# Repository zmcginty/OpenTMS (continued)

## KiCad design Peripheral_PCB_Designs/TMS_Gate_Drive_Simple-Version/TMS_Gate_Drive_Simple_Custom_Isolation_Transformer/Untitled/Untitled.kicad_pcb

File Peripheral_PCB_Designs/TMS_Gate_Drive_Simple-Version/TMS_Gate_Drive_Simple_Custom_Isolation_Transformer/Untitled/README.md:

# FZ1200R33KF2 bolt-on gate driver (rev D, prototype)

Single-channel plug-and-play style gate driver for the Infineon/eupec FZ1200R33KF2
(3300 V / 1200 A IHM single switch). Same external interface as the CONCEPT 1SD418F2:
15 V supply on a 5-pin header (or JST-XH), fiber-optic command in, fiber-optic status out,
2-level / 3-level mode jumper. Built only from catalog parts, with no custom-wound magnetics and no
CONCEPT / Power Integrations ASICs, cores or DC/DC modules. Dynamic advanced active clamping follows the idea used in the
1SP0635 (SCALE-2 plug-and-play).

**Status: design draft, not built or tested. Hazardous voltages. Read "Open items" before ordering anything.**

## Files

| File | What it is |
|---|---|
| `fz1200_gate_driver.kicad_pro/.kicad_sch/.kicad_pcb` | KiCad 7 project (opens in KiCad 8/9; they upgrade it) |
| `power.kicad_sch`, `control.kicad_sch`, `output.kicad_sch` | Sub-sheets: isolation supply, protection logic, output stage + HV |
| `igbt_drv.kicad_sym`, `igbt_drv.pretty/` | Project symbol library and custom footprints (incl. the provisional XS000027 land pattern) |
| `BOM_fz1200_gate_driver.csv` | Grouped BOM (Qty 0 = DNP) |
| `out/` | Gerbers + drill (6 layers), pick-and-place CSV, schematic PDF, per-layer PCB PDFs |
| `generator/` | Python that generates schematic, PCB, routing and BOM from `circuit.py`; `mech.py` holds the mount coordinates |

The schematic and board are generated, so changes are easiest made in `generator/circuit.py`
(parts and nets) and `generator/gen_pcb.py` (placement), then re-run
`python3 generator/gen_sch.py`, `/usr/bin/python3 generator/gen_pcb.py`,
`/usr/bin/python3 generator/patch_fix.py fz1200_gate_driver.kicad_pcb` (CH6 neck-downs and primary ground stitching),
`/usr/bin/python3 generator/fill_zones.py ...`, `/usr/bin/python3 generator/drc.py fz1200_gate_driver.kicad_pcb drc.rpt`,
`/usr/bin/python3 generator/finish.py fz1200_gate_driver.kicad_pcb drc.rpt` (closes the few connections the router leaves open),
`/usr/bin/python3 generator/manual_fix.py fz1200_gate_driver.kicad_pcb drc.rpt` (via-bridges anything still open),
`/usr/bin/python3 generator/cleanup.py fz1200_gate_driver.kicad_pcb`, `/usr/bin/python3 generator/fill_zones.py fz1200_gate_driver.kicad_pcb`,
`python3 generator/gen_bom.py`, `sh generator/export.sh`. If an edit leaves a few opens that finish/manual_fix can't close, `generator/maze_fix.py board drc.rpt` is a fine-grid maze router for them. `python3 generator/check_sides.py` confirms no net crosses the isolation barrier.
You can also just edit the KiCad files by hand from here on.

## Interface (matches 1SD418F2)

| Item | This design | 1SD418F2 |
|---|---|---|
| Supply | J1 1x5 2.54 mm: pin 3 = +15 V, pins 1, 2, 4, 5 = GND (or J2 JST-XH: 1 = +15 V, 2 = GND) | same 5-pin pinout |
| Command | HFBR-2522Z, light = IGBT on | HFBR-2522 |
| Status | HFBR-1522Z, light on = healthy, 0.9 us dark ack on every command edge, about 1.1 s dark on fault | same protocol (1 s) |
| Mode | JP1 1-2 = 2-level (driver turns off on short circuit), 2-3 = 3-level (report only, host turns off). Open = 2-level | J1 jumper, same meaning |
| Gate | +15 / -10 V (set by the catalog transformer), Rg(on) 1.8 ohm, Rg(off) 3.4 ohm, Cge 222 nF | +-15 V, 1.8 / 3.4 ohm, 220 nF |
| Mounting | Screws onto the module G, aux E, aux C terminals (M4), plus a 3.2 mm support hole; terminal positions and outline as on the 1SP0635 (see Board) | same principle |

## Architecture

- **Isolation supply:** TI SN6507 push-pull driver (36 V, two 0.5 A switches, 150 kHz set by R1,
  soft-start and current limit on SS/ILIM) driving a **Poweronics XS000027**, a catalog gate-drive
  transformer for IGBTs up to 3.3 kV: 6 kV isolation test, partial-discharge routine test at 3.545 kV,
  18 kV impulse, 15-0-10 V output, 10 W from a 15 V supply. Rails: VP = +15 V, VE = emitter,
  VEE = -10 V, unregulated (the 1SD418F2 is unregulated too). D3 rectifies the 15 V end and D6 the 10 V end;
  D4/D5 are DNP positions in case Poweronics' reference rectifier uses all four diodes.
- **Logic** is referenced to VEE (the -10 V rail) with a 5 V LDO, so the fiber parts, comparators,
  gates and both gate-driver ICs share one ground with no level shifting.
- **Gate power stage (rev D): Q2 = Infineon ISA170230C04LMDS**, a complementary 40 V OptiMOS dual in
  one SO-8 (N 17 mohm / 38 A pulsed, P 23 mohm / -35 A pulsed, VGS +-20 V), the same family as the
  ISA250250N04LMDS dual-N. Q2 is the only part that carries gate current:
  - **Turn-on:** Q2 P-channel, source at VP (+15 V), drain -> R40 || R41 (2 x 3.6 ohm) -> GATE.
    Its gate is driven between VP and VE (0 / -15 V VGS) by U21 (UCC27511, supplied VP-VE).
    The logic is VEE-referenced, so DRV_ON reaches U21 through a small level shifter:
    Q7 (IRLML0060) pulls LSIN down through R60, D20 (BAT54) clamps it at VE, R61 pulls it up to VP.
    If anything loses power, R61/R64 hold the P-FET off.
  - **Turn-off:** Q2 N-channel, source at VEE (-10 V), drain -> R47 || R48 (2 x 6.8 ohm) -> GATE,
    driven between VE and VEE (10 V VGS) by U22 (UCC27511).
  - Peak currents with these resistors: about 11 A on, 7 A off (25 V swing), so the 35/38 A pulse
    rating is margin. Lower Rg to get more current, the stage is not the limit.
  - C50 (10 uF) and C51 sit right at Q2's two source pins, so the high-current loop is VP-C50-VEE.
  - Why not two ISA250250N04LMDS N-channels: an N-FET high side needs its gate above VP, i.e. a
    bootstrap or charge pump, and a bootstrap can't hold the IGBT on indefinitely (DC on, or long
    on-times at low frequency). The complementary sibling avoids that with the same package and pinout.
  **Soft shutdown** after a fault: Q3 (IRLML0060) through 10 ohm (normal off path held off).
- **Short-circuit (Vce) detection:** 6 x 3.3 Mohm high-voltage chain plus 309 kohm divider into a
  TLV3202 comparator. Trip at Vce = 55.1 V (1SD418F2: 50-60 V), blanking 6.1 us from the on command.
  The fault latches a 1.1 s TLC555 lockout and darkens the status fiber.
- **UVLO:** both rails watched (each comparator channel has its own LM4040 reference, D13/D14):
  VP-VEE trips at 21.5 V rising / 20.3 V falling (nominal 25 V), VE-VEE at 8.5 / 8.1 V (nominal 10 V).
  That's about 86 % of nominal, the same ratio as the 1SD418F2's 13 V threshold on its 15 V supply.
- **Advanced active clamping:** 6 x 1.5SMC440A TVS from collector to gate through SS34 + 10 ohm.
  When clamp current flows, Q4 pulls the gates of the turn-off switches (Q2, Q3) low, so the TVS
  current goes into the gate instead of the off-resistor. This is the "advanced" part.
- **Dynamic AAC (DA2C, as on 1SP0635):** an extra SMBJ188A is in series. Q5 (600 V) shorts it while
  the IGBT is on and for about 17 us after turn-off, then releases it. So the clamp acts at
  2508-2772 V during switching, but the module can sit at a higher DC link when it's off. Q5's gate is
  bootstrapped (C57) so it stays on while the clamp node rises during clamping.

## Key numbers (calculated; the clamp was also checked in a behavioural ngspice model)

| Item | Value |
|---|---|
| Clamp onset, switching (6 x VBR) | 2508-2772 V at 25 C |
| Clamp onset, off-state (DA2C released) | 2717-3003 V |
| TVS stand-off: switching / off-state | 2256 V / 2444 V (in the off state D40 sees at most its 231 V VBR max), so max DC link 2200 V (same as 1SD418F2) |
| Simulated Vce peak, 4 kA turn-off, 100 nH, BV +6 % hot | 2.96 kV (< 3.3 kV) |
| Desat threshold / blanking | 55.1 V / 6.08 us; gate starts falling about 6.3 us, well inside the 10 us SC rating |
| Gate energy per cycle (QG about 19 uC at -10/+15 V, estimated from the 22 uC at +-15 V, + Cge, 25 V swing) | about 0.61 mJ |
| Quiescent load | about 0.5 W (the status LED's 30 mA dominates) |
| Available output | about 6 W, set by the SN6507's 0.5 A switches at 15 V in (the XS000027 is rated 10 W) |
| Max switching frequency | **about 8 kHz** (1SD418F2: 4 kHz) |
| Status ack / fault block | 0.90 us / 1.1 s |

## Board

- 197.1 x 43.94 mm, outline and terminal positions taken from the 1SP0635V mechanical
  drawing (Description & Application Manual, Fig. 5), which bolts onto the same 3.3 kV IHM housing:
  - C (aux collector, X3): 20.04 mm from the left edge, 12.16 mm below the top edge
  - E (aux emitter, X2): C + 38.15 mm, 6.96 mm below the top edge
  - G (gate, X1): E + 21.00 mm, same height
  - 3.2 mm support hole: G + 114.4 mm, 3.95 mm above the bottom edge
  - The notches in the bottom edge and the cut-away under the right end follow the 1SP0635 outline.
    Corners without a dimension were scaled from the drawing (about 0.3 mm) and kept on or inside it.
  The layout follows the 1SP0635's arrangement too: HV chains at the collector (left) end, output
  stage around E/G, logic and fibers in the middle (fiber ports overhang the bottom edge), transformer and
  15 V input at the right end. Rev D: the fibers sit at 10.16 mm pitch so they interlock, and the
  comparator cluster (U19) moved to the bottom side above them, freeing the area under the gate power stage.
- 6 layers: F.Cu parts + signals | In1 VEE plane (PGND under the primary) | In2 signals |
  In3 signals + 5 V logic plane under the logic block | In4 VE (emitter) plane | B.Cu signals + parts.
  At this outline (about 30 % less usable area than rev A) four layers did not route. The comparator
  and UVLO clusters sit on the bottom side; the comparators are TLV3202 in SOIC-8 for easier escape.
- Primary-to-secondary: >= 20 mm copper-to-copper (measured 21.6 mm) with a 2 mm milled slot under T1 (1SD418F2: 20 mm).
- HV creepage is graded along both chains. Low-voltage copper keeps the IEC 60664-1 PD2 /
  material group II creepage for 3300 V (22 mm) from the collector chain. Between HV nets the
  spacing follows each pair's worst-case DC voltage at a 2200 V link, in both DA2C states
  (`generator/potentials.py`). Pairs under 400 V (only inside the Q5/D40 DA2C cluster, where the
  SOT-223 pin pitch alone is below the uncoated value) are held to the coated (IEC 60664-3) value.
  **So conformal coating is mandatory**, and so is FR4 with CTI >= 400.
  `generator/check_creepage.py` reports both the coated and uncoated results.
- Minimum copper clearance rule 0.15 mm (needed by the 0.5 mm-pitch SN6507 land pattern); everything the router placed keeps 0.25 mm or more.
- Routed by a custom router in `generator/gen_pcb.py`; the last few connections are closed by `finish.py`.
- Verification state (rev D as delivered):
  - KiCad DRC: 0 unconnected pads, 0 clearance / hole / edge / short errors. Remaining: 171
    "library not in this configuration" warnings (footprints are embedded in the board; they clear once
    KiCad's standard libraries are in your global table), 13 cosmetic silkscreen warnings (some are the fiber outlines overhanging the edge, intended) and one short
    dead copper stub (harmless; delete it in the editor if you like).
  - Schematic netlist matches the intended circuit net-for-net (85 nets); `check_sides.py` confirms no net crosses the barrier, and the PCB pad nets match the schematic.
  - Terminal positions on the board: C (20.04, 12.16), E (58.19, 6.96), G (79.19, 6.96), support hole
    (193.59, 39.99), i.e. C to E 38.15 mm and E to G 21.00 mm, as in the 1SP0635 drawing.
  - Creepage: primary-secondary 21.7 mm. All HV pairs pass the coated (PD1) limits, and everything at or
    above 400 V passes uncoated PD2. The 3 uncoated shortfalls are 231 V pairs inside the DA2C switch cluster.
  - Courtyards: no overlaps, everything inside the outline.
  - KiCad 7's command line has no schematic ERC, so run ERC once in the GUI.

## Open items before fabrication (in priority order)

1. **Check the fit on a real module.** Terminal positions now come from the 1SP0635 drawing (which
   fits this IHM housing). Before ordering, print the board 1:1 (`out/pcb_top.pdf`) or measure a
   module and confirm C/E/G and the support hole, and that the cut-away clears the main terminals.
2. **Get the XS000027 drawing and reference design from Poweronics** (hello@poweronics.co.uk; they
   offer a reference design, Altium footprint and schematic). Then:
   - Replace the provisional land pattern `XS000027_PROVISIONAL` (primary row and secondary row 24 mm
     apart, so the board keeps 20 mm+ isolation). Keep the 2 mm slot between the rows.
   - Confirm the pin mapping (primary: SW1 / centre tap = +15 V in / SW2; secondary: 15 V end, 0 V = emitter,
     10 V end) and the rectifier: D3 + D6 as drawn, or fit D4/D5 if their reference uses a 4-diode bridge.
   - Confirm the switching frequency range (R1 = 82.5 kohm gives about 150 kHz) and that the
     SN6507's 48 % default duty with 70 ns dead time suits the core.
3. **Optional input UVLO:** EN is tied to VCC through R3 (0 ohm), so the SN6507 starts as soon as VCC
   comes up. Fit R4 and change R3 to a divider if you want a primary-side UVLO as well.
4. **Confirm Q2's channel-to-pin mapping and land pattern** on the full Infineon datasheet. The design
   assumes channel 1 (pins 1 S, 2 G, 7-8 D) = N and channel 2 (pins 3 S, 4 G, 5-6 D) = P, which is
   how the datasheet orders the parameters, and a standard SO-8 (3.9 x 4.9 mm, 1.27 mm) land pattern.
   If it's the other way round, swap the nets in `circuit.py` (Q2) and regenerate.
5. **Fiber connectors (rev D):** footprint `HFBR_Versatile` now follows Broadcom AV02-1501EN: all
   holes 1.01 mm, pins 5 and 8 plated, courtyard = 10.16 mm body width, so U3 and U18 sit at 10.16 mm
   pitch and their molded L-bracket / L-slot tabs interlock. Pin 5/8 row is 2.0 mm from the board
   edge (Broadcom: >= 1.85 mm) and the ports overhang the edge. Pins 5/8 are left unconnected
   (mechanical); tie them to VEE if you want them grounded. Check the order of the two modules: the
   interlock only engages with the L-bracket side of one against the L-slot side of the other.
6. **Validation:** double-pulse at 1800 V and 2200 V (turn-off overshoot with and without DA2C),
   short-circuit test (type I) at 2200 V, blanking margin at full current (the 3.3 kV Vce tail
   must fall below 55 V within about 6 us; increase R20 if not), hipot, partial discharge, thermal
   check of the R(on)/R(off) resistors at the target switching frequency.

## Not included / changed from the original

- Turn-off rail is -10 V instead of -15 V, because that's what the catalog transformer provides. Expect slightly
  slower turn-off and less margin against dv/dt-induced turn-on; verify both in the double-pulse test.
- Isolation transformer: Coilcraft TX2-ZE242x was evaluated and rejected for this module. It is a
  5 kVrms / 10 mm creepage part with no partial-discharge rating, while a 3.3 kV IHM driver needs
  about 6 kVrms test, partial-discharge extinction >= 2.6 kV and >= 20 mm pri-sec spacing (1SD418F2 / IEC 61800-5-1).
  It suits 1200 V modules (1700 V only after your own PD test). The XS000027 stays.
- No overcurrent measurement (the 1SD418F2 has none either); short-circuit detection only.
- References and pin assignments were checked against manufacturer datasheets for the ICs;
  passives are generic (value, voltage, dielectric, package) so you can source them freely.

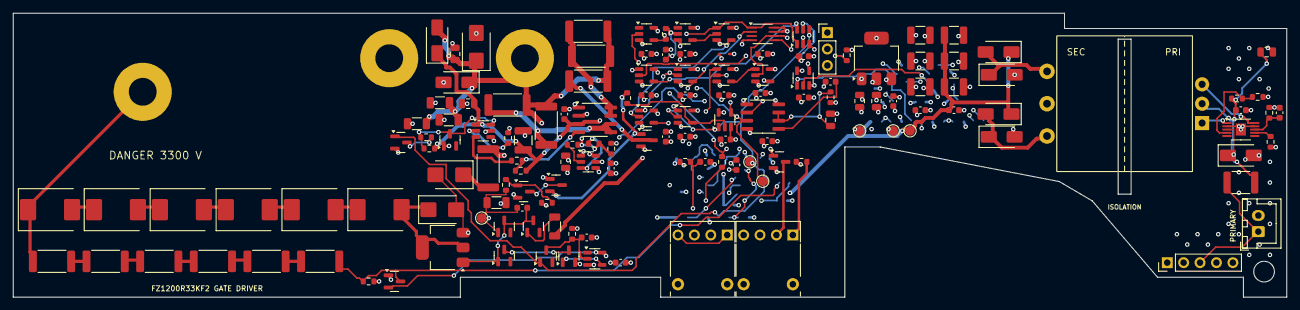
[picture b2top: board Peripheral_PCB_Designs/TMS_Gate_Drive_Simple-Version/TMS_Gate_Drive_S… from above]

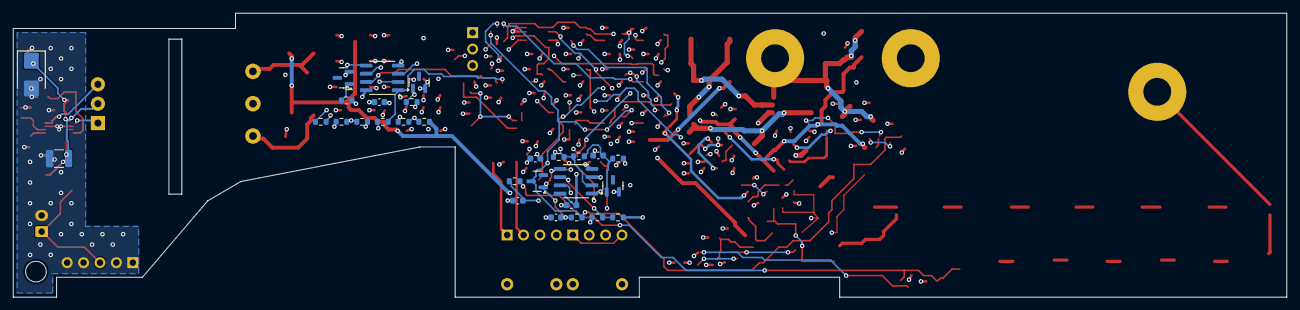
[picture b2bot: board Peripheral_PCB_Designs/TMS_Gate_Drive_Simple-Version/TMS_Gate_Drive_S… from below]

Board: 6 copper layers, 197.1 x 43.9 mm, 175 parts (29 on the bottom side), 85 nets.

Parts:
C1: 22uF 25V X7R; C_1210_3225Metric
C2, C24, C49, C52: 1uF 50V X7R; C_0805_2012Metric
C3, C22, C23, C26, C30, C35, C51, C53, C60, C61, C63, C64, C65, C66, C67, C68, C69, C70, C71, C72, C73, C74, C75, C76: 100nF 50V X7R; C_0603_1608Metric
C4: 470nF 16V X7R; C_0603_1608Metric
C10, C11, C12, C16, C17, C18: 47uF 25V X5R; C_1210_3225Metric
C25: 10uF 16V X7R; C_0805_2012Metric
C31: 150pF C0G; C_0603_1608Metric
C32: 100pF C0G; C_0603_1608Metric
C33: 1uF 16V X7R; C_0805_2012Metric
C34: 10nF 50V X7R; C_0603_1608Metric
C36: 1nF C0G; C_0603_1608Metric
C37: 1nF C0G 1%; C_0603_1608Metric
C38: 47pF C0G; C_0603_1608Metric
C50: 10uF 35V X7R; C_1210_3225Metric
C54, C55: 100nF C0G 50V; C_1206_3216Metric
C56: 22nF C0G 50V; C_0805_2012Metric
C57: 1nF 50V X7R; C_0603_1608Metric
C58: 220pF C0G; C_0603_1608Metric
D1, D3, D4, D5, D6, D37, D38: B1100; D_SMA
D2: SMBJ18A; D_SMB
D10, D13, D14: LM4040-2.5; SOT-23
D11, D42, D43, D44: BAS16; SOT-23
D12: BAT54S; SOT-23
D20: BAT54; SOT-23
D22: BAT54C; SOT-23
D30, D31, D32, D33, D34, D35: 1.5SMC440A; D_SMC
D36: SS34; D_SMB
D39: SMBJ16CA; D_SMB
D40: SMBJ188A; D_SMB
D41: BZX84C12; SOT-23
F1: 0.75A PTC; Fuse_1812_4532Metric
J1: VDC_HDR; PinHeader_1x05_P2.54mm_Vertical
J2: VDC_JST; JST_XH_B2B-XH-A_1x02_P2.50mm_Vertical
JP1: MODE; PinHeader_1x03_P2.54mm_Vertical
Q1, Q3, Q6, Q7: IRLML0060; SOT-23
Q2: ISA170230C04LMDS; SOIC-8_3.9x4.9mm_P1.27mm
Q4: MMBT2222A; SOT-23
Q5: IPN60R600P7S; SOT-223-3_TabPin2
R1: 82.5k 1%; R_0603_1608Metric
R2: 18.2k 1%; R_0603_1608Metric
R3: 0R; R_0603_1608Metric
R4: DNP; R_0603_1608Metric
R10: 10R; R_0603_1608Metric
R11, R15, R37, R51: 1k; R_0603_1608Metric
R12: 13k; R_0603_1608Metric
R13: 1M 1%; R_0603_1608Metric
R14: 100R; R_0603_1608Metric
R16: 15k 1%; R_0603_1608Metric
R17, R19, R22, R25: 10k 1%; R_0603_1608Metric
R18: 5.76k 1%; R_0603_1608Metric
R20: 6.04k 1%; R_0603_1608Metric
R21: 73.2k 1%; R_0603_1608Metric
R23: 332k 1%; R_0603_1608Metric
R24: 23.2k 1%; R_0603_1608Metric
R26: 301k 1%; R_0603_1608Metric
R27, R46, R54, R61, R64: 10k; R_0603_1608Metric
R28, R29: 2.2k; R_0603_1608Metric
R30, R31, R32, R33, R34, R35: 3.3M 1%; R_2512_6332Metric
R36: 309k 1%; R_0603_1608Metric
R40, R41: 3.6R 1W; R_2512_6332Metric
R44: 47R; R_0603_1608Metric
R45, R62, R63: 2R2; R_0603_1608Metric
R47, R48: 6.8R 1W; R_2512_6332Metric
R52, R55: 10R 1W; R_2512_6332Metric
R53: 330R; R_0603_1608Metric
R56: 33k; R_1206_3216Metric
R57: 10k 1%; R_1206_3216Metric
R58: 10k; R_1206_3216Metric
R59: 100k 1%; R_0603_1608Metric
R60: 4.7k; R_0603_1608Metric
T1: XS000027; XS000027_PROVISIONAL
TP1: V5; TestPoint_Pad_D1.5mm
TP3: VE; TestPoint_Pad_D1.5mm
TP4: VP; TestPoint_Pad_D1.5mm
TP5: DRV_ON; TestPoint_Pad_D1.5mm
TP6: BLOCK; TestPoint_Pad_D1.5mm
TP7: CL_A; TestPoint_Pad_D1.5mm
U1: SN6507DGQR; HVSSOP-10-1EP_3x3mm_P0.5mm_EP1.57x1.88mm
U2: TPS7B6950QDCYRQ1; SOT-223-3_TabPin2
U3: HFBR-2522Z; HFBR_Versatile
U4, U23: 74LVC1G14; SOT-23-5
U5: 74LVC1G17; SOT-23-5
U6: 74LVC1G86; SOT-23-5
U7: 74LVC1G74; SSOP-8_2.95x2.8mm_P0.65mm
U8: 74LVC1G32; SOT-23-5
U9: 74LVC1G11; SOT-23-6
U10: 74LVC1G04; SOT-23-5
U11: 74LVC1G00; SOT-23-5
U12, U13: 74LVC1G08; SOT-23-5
U14, U15, U16: 74LVC1G02; SOT-23-5
U17: TLC555CDR; SOIC-8_3.9x4.9mm_P1.27mm
U18: HFBR-1522Z; HFBR_Versatile
U19, U20: TLV3202AIDR; SOIC-8_3.9x4.9mm_P1.27mm
U21, U22: UCC27511DBVR; SOT-23-6
X1: GATE; Terminal_M4
X2: VE; Terminal_M4
X3: CAUX; Terminal_M4

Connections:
ACK: U6.4, U14.2
BASE: Q4.1, R53.2, R54.1
BLK: C37.1, D11.1, R20.2, U19.5
BLK_DONE: U11.2, U19.7
BLOCK: TP6.1, U10.2, U14.1, U17.3
CAUX: D30.1, R30.1, X3.1
CH1: D30.2, D31.1
CH2: D31.2, D32.1
CH3: D32.2, D33.1
CH4: D33.2, D34.1
CH5: D34.2, D35.1
CH6: D35.2, D40.1, Q5.2
CLK: D36.1, R55.1
CL_A: C57.2, D36.2, D40.2, D41.1, Q5.3, R53.1, R56.1, TP7.1
CMD: R12.1, U4.4, U6.1, U7.1, U9.1
CMD_DLY: U5.4, U6.2
CMD_RC: C32.1, R12.2, U5.2
CTRL: C34.1, U17.5
DA_OFF: Q6.1, U23.4
DA_RC: C58.1, D44.3, R59.1, U23.2
DG: C57.1, D41.3, D42.3, D43.1, Q5.1
DGOFF: D43.3, Q6.3
DGR: D42.1, R58.2
DRV_OFF: U16.4, U22.6
DRV_ON: D11.3, D44.1, Q7.1, R20.1, TP5.1, U9.4, U15.2, U16.1
EN: U7.5, U9.3
FCLK: R1.1, U1.7
FO_FLT: C31.1, R11.2, U4.2
FO_RX: R11.1, U3.1, U3.4
GATE: C54.1, C55.1, C56.1, D37.2, D38.1, D39.1, R40.2, R41.2, R47.2, R48.2, R52.2, R55.2, R57.1, X1.1
GP: Q2.4, R62.2, R63.2, R64.1
GPH: R62.1, U21.2
GPL: R63.1, U21.3
GQ: D22.1, Q2.2, R44.2, R45.2, R46.1
GQH: R44.1, U22.2
GQL: R45.1, U22.3
HOLD: D22.3, Q4.3
HVS1: R30.2, R31.1
HVS2: R31.2, R32.1
HVS3: R32.2, R33.1
HVS4: R33.2, R34.1
HVS5: R34.2, R35.1
LED_A: R14.2, U18.1
LED_K: Q1.3, U18.2
LED_ON: Q1.1, U14.4
LSIN: D20.3, R60.2, R61.2, U21.6
LS_D: Q7.3, R60.1
M3L: JP1.2, R27.1, U8.2
NBLOCK: U7.2, U8.1, U10.4, U15.1
NSC: U11.4, U12.1
NUV: U7.6, U12.2, U13.4
OUT_ON: Q2.5, Q2.6, R40.1, R41.1
PEN: R3.2, R4.1, U1.4
PGND: C1.2, C2.2, C3.2, C4.2, D1.2, D2.2, J1.1, J1.2, J1.4, J1.5, J2.2, R1.2, R2.2, R4.2, U1.2, U1.9, U1.11
ROFF_D: Q2.7, Q2.8, R47.1, R48.1
RSSD_D: Q3.3, R52.1
SEC_A: D3.2, D5.1, T1.4
SEC_B: D4.2, D6.1, T1.6
SG: D22.2, Q3.1, R51.2
SNS: D12.3, R35.2, R36.1, R37.1
SNS_F: C38.1, R37.2, U19.3
SSD_ON: R51.1, U15.4, U16.2
SSILIM: C4.1, R2.1, U1.8
SW1: T1.1, U1.1
SW2: T1.3, U1.10
TRIG_N: U12.4, U17.2
T_RC: C33.1, R13.2, U17.6, U17.7
UVE_OK: R26.1, U13.2, U20.7
UVE_S: R24.2, R25.1, R26.2, U20.5
UVP_OK: R23.1, U13.1, U20.1
UVP_S: R21.2, R22.1, R23.2, U20.3
V5: C25.1, C26.1, C60.1, C61.1, C63.1, C64.1, C65.1, C66.1, C67.1, C68.1, C69.1, C70.1, C71.1, C72.1, C73.1, C74.1, C75.1, C76.1, D12.2, JP1.3, R10.1, R13.1, R14.1, R15.1, R18.1, R28.1, R29.1, TP1.1, U2.3, U4.5, U5.5, U6.5, U7.7, U7.8, U8.5, U9.5, U10.5, U11.5, U12.5, U13.5, U14.5, U15.5, U16.5, U17.4, U17.8, U19.8, U20.8, U23.5
VBT: R18.2, R19.1, U19.6
VCE_HI: U11.1, U19.1
VE: C10.2, C11.2, C12.2, C16.1, C17.1, C18.1, C22.2, C23.1, C24.1, C49.2, C52.1, C53.1, C54.2, C55.2, C56.2, D20.1, D39.2, R24.1, R57.2, T1.5, TP3.1, U2.1, U21.4, U21.5, U22.1, X2.1
VEE: C16.2, C17.2, C18.2, C23.2, C24.2, C25.2, C26.2, C30.2, C31.2, C32.2, C33.2, C34.2, C35.2, C36.2, C37.2, C38.2, C50.2, C51.2, C52.2, C53.2, C58.2, C60.2, C61.2, C63.2, C64.2, C65.2, C66.2, C67.2, C68.2, C69.2, C70.2, C71.2, C72.2, C73.2, C74.2, C75.2, C76.2, D5.2, D6.2, D10.2, D12.1, D13.2, D14.2, D38.2, JP1.1, Q1.2, Q2.1, Q3.2, Q4.2, Q6.2, Q7.2, R17.2, R19.2, R22.2, R25.2, R27.2, R36.2, R46.2, R54.2, R56.2, R59.2, U2.2, U3.2, U4.3, U5.3, U6.3, U7.4, U8.3, U9.2, U10.3, U11.3, U12.3, U13.3, U14.3, U15.3, U16.3, U17.1, U19.4, U20.4, U22.4, U22.5, U23.3
VIN: C1.1, C2.1, C3.1, D1.1, D2.1, F1.2, R3.1, T1.2, U1.3
VIN_R: F1.1, J1.3, J2.1
VP: C10.1, C11.1, C12.1, C22.1, C49.1, C50.1, C51.1, D3.1, D4.1, D37.1, Q2.3, R21.1, R58.1, R61.1, R64.2, TP4.1, U21.1
VREF1: C36.1, R16.2, R17.1, U19.2
VREF25: C35.1, D10.1, R15.2, R16.1
VREF_UV: D13.1, R28.2, U20.2
VREF_UV2: D14.1, R29.2, U20.6
VRX: C30.1, R10.2, U3.3
XOK: U8.4, U9.6

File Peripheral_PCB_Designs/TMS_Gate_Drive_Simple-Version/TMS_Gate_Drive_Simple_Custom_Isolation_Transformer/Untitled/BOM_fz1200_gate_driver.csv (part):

Item,Qty,References,Value,Footprint,Manufacturer,MPN,DNP,Notes
1,1,J1,VDC_HDR,PinHeader_1x05_P2.54mm_Vertical,Amphenol ICC (FCI),77315-101-05LF,,"Primary supply, same pinout as 1SD418F2 (3=VDC, others GND)"
2,1,J2,VDC_JST,JST_XH_B2B-XH-A_1x02_P2.50mm_Vertical,JST,B2B-XH-A(LF)(SN),,Alternate supply connector (fit J1 or J2)
3,1,JP1,MODE,PinHeader_1x03_P2.54mm_Vertical,Samtec,TSW-103-07-T-S,,"1-2: 2-level, 2-3: 3-level/multilevel"
4,1,X1,GATE,Terminal_M4,,"M4 screw, spring washer",,Screw terminal to module aux pin
5,1,X2,VE,Terminal_M4,,"M4 screw, spring washer",,Screw terminal to module aux pin
6,1,X3,CAUX,Terminal_M4,,"M4 screw, spring washer",,Screw terminal to module aux pin
7,1,T1,XS000027,XS000027_PROVISIONAL,Poweronics,XS000027,,"Push-pull forward gate-drive transformer, 15-0-10 V, 10 W, for IGBTs up to 3.3 kV, 6 kV test, PD routine test 3.545 kV. PINOUT/FOOTPRINT PROVISIONAL: confirm with Poweronics drawing"
8,1,U1,SN6507DGQR,HVSSOP-10-1EP_3x3mm_P0.5mm_EP1.57x1.88mm,Texas Instruments,SN6507DGQR,,"36 V push-pull transformer driver; DC and SR left open = 48 % duty, default slew"
9,1,U2,TPS7B6950QDCYRQ1,SOT-223-3_TabPin2,Texas Instruments,TPS7B6950QDCYRQ1,,"5 V logic rail, referenced to VEE"
10,1,U3,HFBR-2522Z,HFBR_Versatile,Broadcom,HFBR-2522Z,,"1 MBd command receiver, light = IGBT on"
11,2,U4 U23,74LVC1G14,SOT-23-5,Texas Instruments,SN74LVC1G14DBVR,,"DA2C hold timer, inverting; Schmitt inverter: light on = CMD high"
12,1,U5,74LVC1G17,SOT-23-5,Texas Instruments,SN74LVC1G17DBVR,,Schmitt buffer
13,1,U6,74LVC1G86,SOT-23-5,Texas Instruments,SN74LVC1G86DBVR,,XOR acknowledge pulse
14,1,U7,74LVC1G74,SSOP-8_2.95x2.8mm_P0.65mm,Texas Instruments,SN74LVC1G74DCTR,,Enable latch sampled on rising command
15,1,U8,74LVC1G32,SOT-23-5,Texas Instruments,SN74LVC1G32DBVR,,Mode gate: 3-level mode ignores fault until host turns off
16,1,U9,74LVC1G11,SOT-23-6,Texas Instruments,SN74LVC1G11DBVR,,Drive enable AND
17,1,U10,74LVC1G04,SOT-23-5,Texas Instruments,SN74LVC1G04DBVR,,Inverter
18,1,U11,74LVC1G00,SOT-23-5,Texas Instruments,SN74LVC1G00DBVR,,Short-circuit detect NAND
19,2,U12 U13,74LVC1G08,SOT-23-5,Texas Instruments,SN74LVC1G08DBVR,,Fault OR (active low); UVLO combine
20,3,U14 U15 U16,74LVC1G02,SOT-23-5,Texas Instruments,SN74LVC1G02DBVR,,Normal turn-off select; Soft shutdown select; Status light drive
21,1,U17,TLC555CDR,SOIC-8_3.9x4.9mm_P1.27mm,Texas Instruments,TLC555CDR,,1.1 s fault blocking one-shot
22,1,U18,HFBR-1522Z,HFBR_Versatile,Broadcom,HFBR-1522Z,,"1 MBd status transmitter, light = healthy"
23,2,U19 U20,TLV3202AIDR,SOIC-8_3.9x4.9mm_P1.27mm,Texas Instruments,TLV3202AIDR,,UVLO comparators; Vce and blanking comparators
24,2,U21 U22,UCC27511DBVR,SOT-23-6,Texas Instruments,UCC27511DBVR,,"N-FET gate driver, supply VE-VEE = 10 V; P-FET gate driver, supply VP-VE = 15 V"
25,4,Q1 Q3 Q6 Q7,IRLML0060,SOT-23,Infineon,IRLML0060TRPBF,,Soft shutdown switch; Status LED switch; Turn-on level shifter VEE->VE; Turns Q5 off after delay
26,1,Q2,ISA170230C04LMDS,SOIC-8_3.9x4.9mm_P1.27mm,Infineon,ISA170230C04LMDSXTMA1,,"35/38 A gate power stage: complementary 40 V OptiMOS, ch1 N 17 mohm (turn-off), ch2 P 23 mohm (turn-on)"
27,1,Q4,MMBT2222A,SOT-23,Diodes Inc,MMBT2222A-7-F,,AAC: disables turn-off switches during clamping
28,1,Q5,IPN60R600P7S,SOT-223-3_TabPin2,Infineon,IPN60R600P7SATMA1,,"DA2C shorting switch, 600 V"
29,5,D1 D3 D6 D37 D38,B1100,D_SMA,Diodes Inc,B1100-13-F,,"+15 V rectifier (15 V end of secondary); -10 V rectifier (10 V end of secondary); Gate clamp to VEE; Gate clamp to VP; Reverse polarity shunt, 100 V 1 A"
30,1,D2,SMBJ18A,D_SMB,Littelfuse,SMBJ18A,,Input TVS
31,0,D4 D5,B1100,D_SMA,Diodes Inc,B1100-13-F,DNP,DNP unless the Poweronics reference rectifier uses it
32,3,D10 D13 D14,LM4040-2.5,SOT-23,Texas Instruments,LM4040BIM3X-2.5/NOPB,,2.5 V reference; Local 2.5 V reference for UVLO; Local 2.5 V reference for UVLO channel 2
33,4,D11 D42 D43 D44,BAS16,SOT-23,Nexperia,"BAS16,215",,"Bootstrap blocking; Fast blanking reset (pin1 A, pin3 K); Fast charge of hold timer"
34,1,D12,BAT54S,SOT-23,Nexperia,"BAT54S,215",,Sense node clamp
35,1,D20,BAT54,SOT-23,Nexperia,"BAT54,215",,Clamps LSIN >= VE - 0.3 V (U21 IN+ abs. min -5 V)
36,1,D22,BAT54C,SOT-23,Nexperia,"BAT54C,215",,Common-cathode OR
37,6,D30 D31 D32 D33 D34 D35,1.5SMC440A,D_SMC,Littelfuse,1.5SMC440A,,Active clamp stack
38,1,D36,SS34,D_SMB,Generic (MCC/Vishay),SS34,,"Clamp blocking diode, 40 V 3 A"
39,1,D39,SMBJ16CA,D_SMB,Littelfuse,SMBJ16CA,,Gate-emitter bidirectional TVS
40,1,D40,SMBJ188A,D_SMB,Littelfuse,SMBJ188A,,DA2C switchable TVS (raises off-state clamp by 209-231 V)
41,1,D41,BZX84C12,SOT-23,Diodes Inc,BZX84C12-7-F,,Q5 Vgs clamp 12 V
42,1,F1,0.75A PTC,Fuse_1812_4532Metric,Bourns,MF-MSMF075/24-2,,"Resettable fuse, 24 V, reverse-polarity trip"
43,1,R1,82.5k 1%,R_0603_1608Metric,Generic,"(any, see Value)",,fsw about 150 kHz (TI); confirm against the XS000027 rating
44,1,R2,18.2k 1%,R_0603_1608Metric,Generic,"(any, see Value)",,Switch current limit (TI typical-application value)
45,1,R3,0R,R_0603_1608Metric,Generic,"(any, see Value)",,EN tied to VCC: self-start
46,0,R4,DNP,R_0603_1608Metric,Generic,"(any, see Value)",DNP,Optional EN/UVLO divider lower leg
47,1,R10,10R,R_0603_1608Metric,Generic,"(any, see Value)",,
48,4,R11 R15 R37 R51,1k,R_0603_1608Metric,Generic,"(any, see Value)",,Input glitch filter
49,1,R12,13k,R_0603_1608Metric,Generic,"(any, see Value)",,0.9 us acknowledge delay
50,1,R13,1M 1%,R_0603_1608Metric,Generic,"(any, see Value)",,1.1 s with C33
51,1,R14,100R,R_0603_1608Metric,Generic,"(any, see Value)",,Status LED about 30 mA
52,1,R16,15k 1%,R_0603_1608Metric,Generic,"(any, see Value)",,1.00 V desat reference
53,4,R17 R19 R22 R25,10k 1%,R_0603_1608Metric,Generic,"(any, see Value)",,
54,1,R18,5.76k 1%,R_0603_1608Metric,Generic,"(any, see Value)",,Blanking threshold 63.4% V5
55,1,R20,6.04k 1%,R_0603_1608Metric,Generic,"(any, see Value)",,Blanking 6.1 us
56,1,R21,73.2k 1%,R_0603_1608Metric,Generic,"(any, see Value)",,VP-VEE trip 21.5 V rising / 20.3 V falling
57,1,R23,332k 1%,R_0603_1608Metric,Generic,"(any, see Value)",,Hysteresis
58,1,R24,23.2k 1%,R_0603_1608Metric,Generic,"(any, see Value)",,VE-VEE trip 8.5 V rising / 8.1 V falling
59,1,R26,301k 1%,R_0603_1608Metric,Generic,"(any, see Value)",,Hysteresis
60,5,R27 R46 R54 R61 R64,10k,R_0603_1608Metric,Generic,"(any, see Value)",,Defaults to 2-level mode; Holds P-FET off without U21 supply; Level shifter pull-up: Q7 off -> P-FET off (fail-safe)
61,2,R28 R29,2.2k,R_0603_1608Metric,Generic,"(any, see Value)",,
62,6,R30 R31 R32 R33 R34 R35,3.3M 1%,R_2512_6332Metric,Vishay,CRHV2512AF3M30FKE5,,Vce sense chain
63,1,R36,309k 1%,R_0603_1608Metric,Generic,"(any, see Value)",,Sets 55.1 V desat threshold with VE-VEE = 10 V
64,2,R40 R41,3.6R 1W,R_2512_6332Metric,Generic,"(any, see Value)",,Rg(on) 2x parallel = 1.8 ohm (as 1SD418F2)
65,1,R44,47R,R_0603_1608Metric,Generic,"(any, see Value)",,Turn-on of Q2N slow so Q4 can override
66,3,R45 R62 R63,2R2,R_0603_1608Metric,Generic,"(any, see Value)",,P-FET turn-off (gate to VP); P-FET turn-on (gate to VE)
67,2,R47 R48,6.8R 1W,R_2512_6332Metric,Generic,"(any, see Value)",,Rg(off) 2x parallel = 3.4 ohm (as 1SD418F2)
68,2,R52 R55,10R 1W,R_2512_6332Metric,Generic,"(any, see Value)",,Clamp feed; Soft shutdown resistor
69,1,R53,330R,R_0603_1608Metric,Generic,"(any, see Value)",,
70,1,R56,33k,R_1206_3216Metric,Generic,"(any, see Value)",,
71,1,R57,10k 1%,R_1206_3216Metric,Generic,"(any, see Value)",,
72,1,R58,10k,R_1206_3216Metric,Generic,"(any, see Value)",,Q5 gate pull-up
73,1,R59,100k 1%,R_0603_1608Metric,Generic,"(any, see Value)",,Hold time about 17 us with C58
74,1,R60,4.7k,R_0603_1608Metric,Generic,"(any, see Value)",,Level shifter series resistor (2 mA)
75,1,C1,22uF 25V X7R,C_1210_3225Metric,Generic,"(any, see Value)",,
76,4,C2 C24 C49 C52,1uF 50V X7R,C_0805_2012Metric,Generic,"(any, see Value)",,
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
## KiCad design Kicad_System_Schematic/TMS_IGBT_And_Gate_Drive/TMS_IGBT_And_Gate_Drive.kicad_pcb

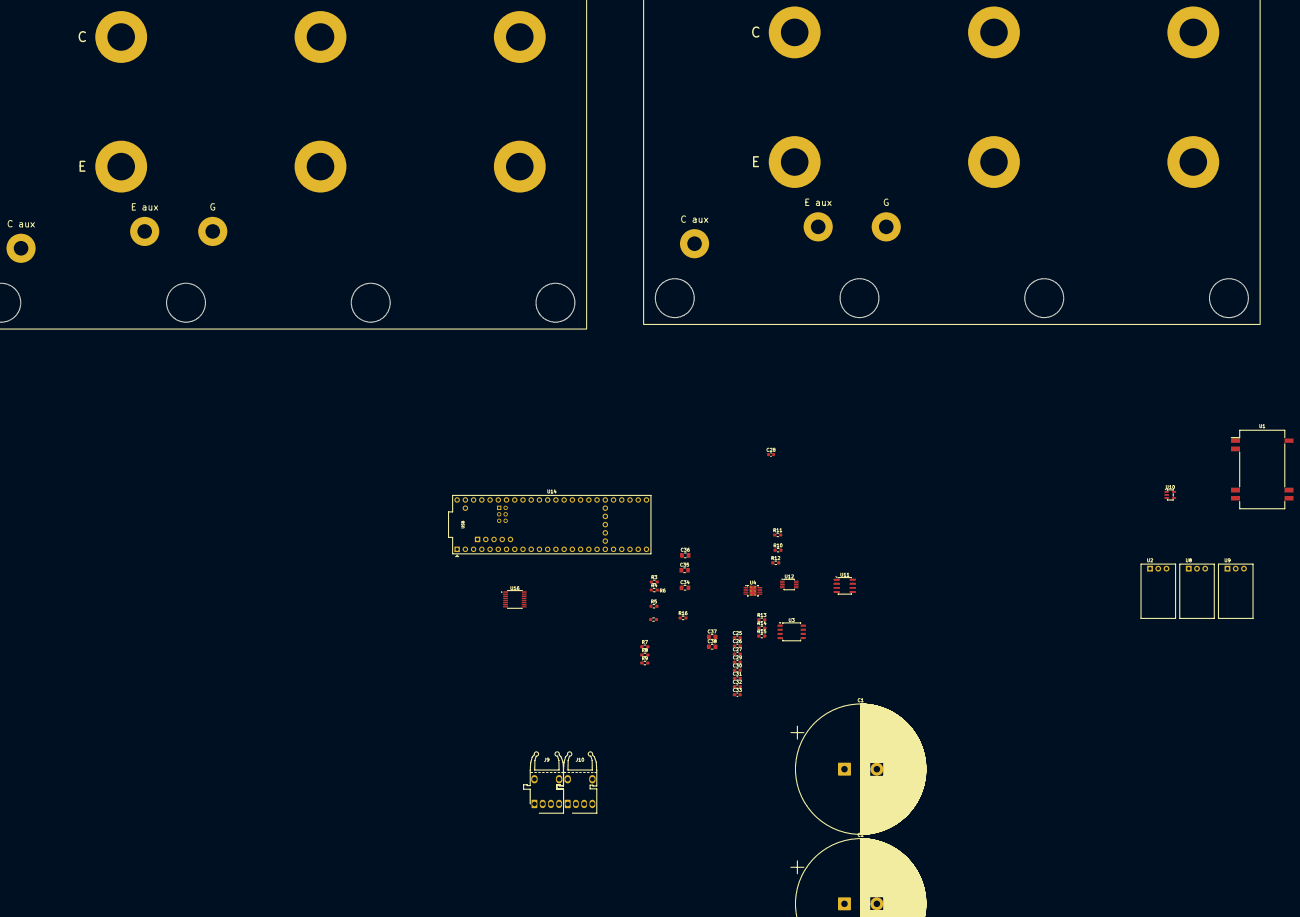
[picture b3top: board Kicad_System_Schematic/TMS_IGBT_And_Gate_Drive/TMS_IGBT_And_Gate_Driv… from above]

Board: 2 copper layers, 45 parts (0 on the bottom side), 24 nets, no tracks yet.

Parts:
C1, C2: 1050µF 1.8kV; CP_Radial_D40.0mm_P10.00mm_SnapIn
C25, C30, C32: 1u; C_0603_1608Metric_Pad1.08x0.95mm_HandSolder
C26, C31: 0.1u; C_0603_1608Metric_Pad1.08x0.95mm_HandSolder
C27, C29, C33: 10u; C_0603_1608Metric_Pad1.08x0.95mm_HandSolder
C28: 10000p; C_0603_1608Metric
C34: 4u7; C_0805_2012Metric_Pad1.18x1.45mm_HandSolder
C35, C37: 1u; C_0805_2012Metric_Pad1.18x1.45mm_HandSolder
C36, C38: 10u; C_0805_2012Metric_Pad1.18x1.45mm_HandSolder
J9: AFBR-2624Z; AGILENT_HFBR-252x
J10: HFBR-1522Z; AGILENT_HFBR-152x
Q1, Q2: FZ1200R33KF2; Infineon_IHV-A_190x140mm_SingleSwitch
R3, R4, R5, R12, R13, R14: 5k1; R_0603_1608Metric_Pad0.98x0.95mm_HandSolder
R6, R9, R10, R11: 0; R_0603_1608Metric_Pad0.98x0.95mm_HandSolder
R7, R8, R15, R16: R; R_0603_1608Metric_Pad0.98x0.95mm_HandSolder
U1: Isolated DC-DC Converter; Converter_DCDC_Artesyn_ATA_SMD
U2, U8, U9: Non-Isolated DC-DC Converter; Converter_DCDC_Murata_OKI-78SR_Horizontal
U3: LM393; SOIC-8_5.3x5.3mm_P1.27mm
U4: AD5693RxRM; AD5683RARMZ
U10: MCP1415; SOT-23-5
U11: LM2931-5.0_SO8; SOIC-8_3.9x4.9mm_P1.27mm
U12: ADS1115IDGS; TSSOP-10_3x3mm_P0.5mm
U14: Teensy_4.1
U16: ADS8699IPWR

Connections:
+3V3: C32.2, C33.2, U8.3 (OUT)
+5V: U2.3 (OUT), U8.1 (IN), U14.48 (VIN)
+5V_LDO: C25.1, C26.1, C27.1, C29.1, C30.1, C31.1, C37.1, C38.1, R3.1, R4.1, R5.1, R6.1, R10.1, R12.1, R13.1, R14.1, U11.1 (OUT)
+7V5: U9.3 (OUT), U11.8 (IN)
+24V: U1.16 (+VIN), U2.1 (IN), U9.1 (IN)
/ADC_INT: R12.2, U12.2 (ALERT/RDY)
/ADC_SCL: R13.2, U12.10 (SCL)
/ADC_SDA: R14.2, U12.9 (SDA)
/Charge_Switch: J9.4 (Fiber_In), J10.4 (Fiber_Out_4)
/DAC_SCL: R3.2, U14.41 (19/A5/SCL)
/DAC_SDA: R4.2, U14.40 (18/A4/SDA)
/INT_ADC_0: R7.1, U14.36 (14/A0/TX3/SPDIF_OUT)
/INT_ADC_1: R8.1, U14.37 (15/A1/RX3/SPDIF_IN)
/INT_ADC_IN_CAP_V: R7.2, R15.2
/INT_ADC_IN_DAC: R8.2, R16.2
GND: C1.2, C2.2, C25.2, C26.2, C27.2, C28.2, C29.2, C30.2, C31.2, C32.1, C33.1, C34.2, C35.2, C36.2, C37.2, C38.2, Q2.4 (Emitter_phase_1), R9.2, R11.2, R15.1, R16.1, U1.1 (-VIN), U2.2 (GND), U8.2 (GND), U9.2 (GND), U11.2 (GND), U11.3 (GND), U11.6 (GND), U11.7 (GND), U12.3 (GND), U12.5 (AIN1), U12.6 (AIN2), U12.7 (AIN3), U12.8 (VDD), U14.1 (GND), U14.34 (GND), U14.47 (GND), U14.52 (GND), U14.58 (GND), U14.59 (GND), U14.64 (GND)
ISO_+15V: U1.9 (+VOUT), U10.2 (Vdd)
ISO_GND: U1.10 (-VOUT), U10.4 (GND)
unnamed: C1.1, C2.1, Q1.4 (Emitter_phase_1)
unnamed: J9.1 (Data_Out), U10.3 (IN)
unnamed: R6.2, R9.1
unnamed: R10.2, R11.1, U12.1 (ADDR)
unnamed: U3.3 (+), U12.4 (AIN0)
unnamed: C35.1, C36.1

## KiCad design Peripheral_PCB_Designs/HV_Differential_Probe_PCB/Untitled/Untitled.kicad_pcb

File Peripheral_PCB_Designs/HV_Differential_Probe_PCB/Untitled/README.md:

# HV differential probe v1 — KiCad project

7 kV / 1000:1 / ~100 MHz (simulated) differential probe, generated from the design doc
"7 kV / 50 MHz High-Voltage Differential Probe — Design v1".

Open `hvprobe.kicad_pro` in KiCad 7 or newer. Files:

| File | What |
| --- | --- |
| `hvprobe.kicad_sch` | Schematic (one A3 sheet, net-label style) |
| `hvprobe.kicad_pcb` | 2-layer board, 232 × 44 mm, fully routed |
| `hvprobe.kicad_sym`, `hvprobe.pretty/` | Project parts: THS4631, TPS7A4901, TPS7A3001, TMR 3-0523, BAV199, GDT, coax pads |
| `fab/` | Gerbers, drill file, pick-and-place CSV |
| `hvprobe-bom.csv` | Grouped BOM |
| `generator/` | Python that produced all of the above (`make_all.py`) |

## What has been checked

- Schematic netlist exported with `kicad-cli` matches the intended netlist exactly (54 nets).
- PCB DRC (KiCad 7.0.11): 0 unconnected pads, 0 clearance / short / hole errors.
  Remaining warnings: 13 silkscreen overlaps (cosmetic), plus "library not in configuration"
  notices that come from the headless build machine and disappear in a normal KiCad install.
- Footprint pinouts checked against datasheets: THS4631 (SOIC-8), TPS7A49/TPS7A30 (MSOP-8 PowerPAD),
  TMR 3 (SIP-8, pin 4 absent), BAV199 (pin 1 A1, 2 K2, 3 K1/A2).

## Not checked — do before ordering

1. **ERC** was not run (KiCad 7's command line has no ERC). Run Inspect → ERC once in the GUI.
2. **GDT footprint** (`GDT_Bourns_2051`) uses estimated pads; compare against the Bourns 2051 land pattern.
3. **HV spacing**: strings are on a 10 mm pitch, the two legs are 24 mm apart with a 3 mm milled slot, and there is no
   copper under the HV area. Confirm creepage against IEC 60664-1 for your working voltage, and conformal-coat the HV area.
4. **Netclass HV** (`HV_*`) uses 1.5 mm clearance, which is right for the 700 V-per-segment spacing; any edits near the
   strings must keep it.
5. Print the board 1:1 and check that the trimmers, pots and TMR module fit.

## Differences from the design doc

- Rtip (330 Ω) is on the board at the input pads instead of in the clip.
- The difference amp uses four discrete 0.1 % resistors instead of a matched network; the DC CMRR trim absorbs the mismatch.
- Battery/USB OR-ing uses two Schottky diodes (B5819W) instead of an ideal-diode IC; USB still gives ~4.7 V, inside the TMR's 4.5–9 V range.
- The output is a captive coax soldered to pads (with tie-wrap holes) rather than an on-board BNC.
- Two layers instead of four; the bottom layer is a near-solid ground plane under the amplifiers.
- Board is 232 mm long: about 120 mm of HV strings, plus the amplifiers and an isolated power section.

## Trims (silkscreen labels)

`GAIN` = RV101, `CMRR DC` = RV201, `FLAT +` = C113, `CMRR AC` = C213, `OFFSET` = RV301. Follow the calibration
procedure in the design doc. C112/C212 are select-on-test pads (DNP by default).

## Regenerating

`python3 generator/make_all.py` needs KiCad 7 (pcbnew Python), kiutils, Java 21 and Freerouting 1.9.
The autorouter is not deterministic, so a rerun gives a different (but DRC-checked) routing. One GND stitching via
next to C115 was added by hand after the final route.

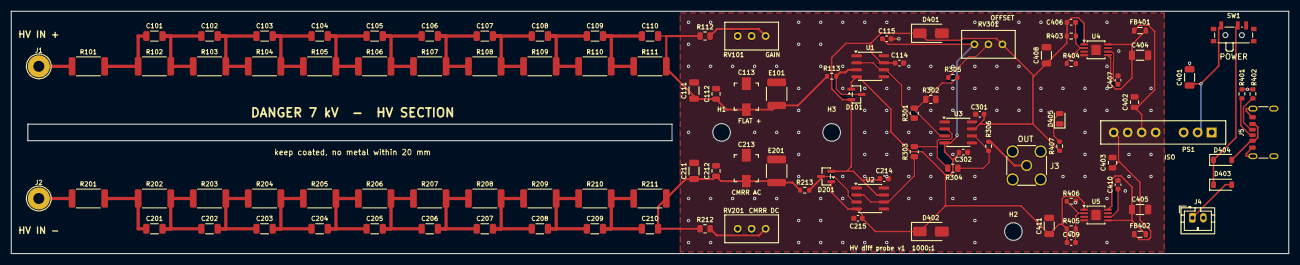
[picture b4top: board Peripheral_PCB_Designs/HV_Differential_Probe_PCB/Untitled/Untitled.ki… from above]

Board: 2 copper layers, 232.0 x 44.0 mm, 111 parts (0 on the bottom side), 54 nets.

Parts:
C101, C102, C103, C104, C105, C106, C107, C108, C109, C110, C201, C202, C203, C204, C205, C206, C207, C208, C209, C210: 22pF 2kV; C_1206_3216Metric
C111, C211: 2.2nF C0G 1%; C_1206_3216Metric
C112, C212: SOT 0-150pF; C_0805_2012Metric
C113, C213: 5-30pF; C_Trimmer_Murata_TZB4-A
C114, C115, C214, C215, C301, C302: 100nF; C_0603_1608Metric
C401, C404, C405, C408, C411: 10uF 25V; C_1206_3216Metric
C402, C403: 1uF 25V; C_0805_2012Metric
C406, C407, C409, C410: 10nF; C_0603_1608Metric
D101, D201: BAV199; SOT-23
D401, D402: SMAJ15CA; D_SMA
D403, D404: B5819W; D_SOD-123
D405: GRN; LED_0805_2012Metric
E101, E201: 90V GDT; GDT_Bourns_2051
FB401, FB402: 600R@100MHz; L_0805_2012Metric
H1, H2, H3: M3; MountingHole_3.2mm_M3
J1: HV_IN_P; TestPoint_THTPad_D4.0mm_Drill2.0mm
J2: HV_IN_N; TestPoint_THTPad_D4.0mm_Drill2.0mm
J3: OUT; SMA_Amphenol_132291_Vertical
J4: BATT 4.5-9V; JST_PH_B2B-PH-K_1x02_P2.00mm_Vertical
J5: USB-C 5V; USB_C_Receptacle_GCT_USB4125-xx-x_6P_TopMnt_Horizontal
PS1: TMR 3-0523; Traco_TMR3_SIP8
R101, R201: 330; R_2512_6332Metric
R102, R103, R104, R105, R106, R107, R108, R109, R110, R111, R202, R203, R204, R205, R206, R207, R208, R209, R210, R211: 10M; R_2512_6332Metric
R112, R212: 97.6k 0.1%; R_0805_2012Metric
R113, R213: 100; R_0603_1608Metric
R301, R302, R303, R304: 1.00k 0.1%; R_0805_2012Metric
R305: 1M; R_0603_1608Metric
R306: 49.9; R_0603_1608Metric
R401, R402: 5.1k; R_0603_1608Metric
R403, R405: 90.9k; R_0603_1608Metric
R404, R406: 10k; R_0603_1608Metric
R407: 4.7k; R_0603_1608Metric
RV101, RV201: 5k; Potentiometer_Bourns_3296W_Vertical
RV301: 10k; Potentiometer_Bourns_3296W_Vertical
SW1: POWER; SW_SPDT_PCM12
U1, U2, U3: THS4631D; SOIC-8_3.9x4.9mm_P1.27mm
U4: TPS7A4901DGNR; MSOP-8-1EP_3x3mm_P0.65mm_EP1.68x1.88mm
U5: TPS7A3001DGNR; MSOP-8-1EP_3x3mm_P0.65mm_EP1.68x1.88mm

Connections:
+12V: C114.1, C214.1, C301.1, C406.1, C408.1, D101.2 (K2), D201.2 (K2), D401.1 (A1), R403.1, R407.1, RV301.1, U1.7 (V+), U2.7 (V+), U3.7 (V+), U4.1 (OUT)
-12V: C115.1, C215.1, C302.1, C409.1, C411.1, D101.1 (A1), D201.1 (A1), D402.1 (A1), R405.1, RV301.3, U1.4 (V-), U2.4 (V-), U3.4 (V-), U5.1 (OUT)
/+15F: C404.1, FB401.2, U4.5 (EN), U4.8 (IN)
/+15V: C402.1, FB401.1, PS1.6 (+Vout)
/-15F: C405.1, FB402.2, U5.5 (EN), U5.8 (IN)
/-15V: C403.1, FB402.1, PS1.8 (-Vout)
/AN: R303.2, R304.1, U3.2 (-)
/AOUT: R304.2, R306.1, U3.6
/AP: R301.2, R302.1, R305.2, U3.3 (+)
/BIN_N: D201.3 (K1A2), R213.2, U2.3 (+)
/BIN_P: D101.3 (K1A2), R113.2, U1.3 (+)
/BOT_N: C210.2, C211.1, C212.1, C213.1, E201.1, R211.2, R212.1, R213.1
/BOT_P: C110.2, C111.1, C112.1, C113.1, E101.1, R111.2, R112.1, R113.1
/BUF_N: R303.1, U2.2 (-), U2.6
/BUF_P: R301.1, U1.2 (-), U1.6
/CC1: J5.A5 (CC1), R401.1
/CC2: J5.B5 (CC2), R402.1
/FB_NEG: C409.2, R405.2, R406.1, U5.2 (FB)
/FB_POS: C406.2, R403.2, R404.1, U4.2 (FB)
/HV_INN: J2.1 (Pin_1_1), R201.1
/HV_INP: J1.1 (Pin_1_1), R101.1
/HV_N0: C201.1, R201.2, R202.1
/HV_N1: C201.2, C202.1, R202.2, R203.1
/HV_N2: C202.2, C203.1, R203.2, R204.1
/HV_N3: C203.2, C204.1, R204.2, R205.1
/HV_N4: C204.2, C205.1, R205.2, R206.1
/HV_N5: C205.2, C206.1, R206.2, R207.1
/HV_N6: C206.2, C207.1, R207.2, R208.1
/HV_N7: C207.2, C208.1, R208.2, R209.1
/HV_N8: C208.2, C209.1, R209.2, R210.1
/HV_N9: C209.2, C210.1, R210.2, R211.1
/HV_P0: C101.1, R101.2, R102.1
/HV_P1: C101.2, C102.1, R102.2, R103.1
/HV_P2: C102.2, C103.1, R103.2, R104.1
/HV_P3: C103.2, C104.1, R104.2, R105.1
/HV_P4: C104.2, C105.1, R105.2, R106.1
/HV_P5: C105.2, C106.1, R106.2, R107.1
/HV_P6: C106.2, C107.1, R107.2, R108.1
/HV_P7: C107.2, C108.1, R108.2, R109.1
/HV_P8: C108.2, C109.1, R109.2, R110.1
/HV_P9: C109.2, C110.1, R110.2, R111.1
/LED_A: D405.2 (A), R407.2
/NR_NEG: C410.1, U5.6 (NR/SS)
/NR_POS: C407.1, U4.6 (NR/SS)
/OFFS: R305.1, RV301.2
/OUT: J3.1 (In), R306.2
/TRIM_N: R212.2, RV201.1
/TRIM_P: R112.2, RV101.1
/VBAT: D403.2 (A), J4.1
/VBUS: D404.2 (A), J5.A9 (VBUS), J5.B9 (VBUS)
/VIN_GND: C401.2, J4.2, J5.A12 (GND), J5.B12 (GND), J5.SH (SHIELD), PS1.1 (-Vin), R401.2, R402.2
/VIN_OR: D403.1 (K), D404.1 (K), SW1.2 (B)
/VIN_SW: C401.1, PS1.2 (+Vin), SW1.1 (A)
GND: C111.2, C112.2, C113.2, C114.2, C115.2, C211.2, C212.2, C213.2, C214.2, C215.2, C301.2, C302.2, C402.2, C403.2, C404.2, C405.2, C407.2, C408.2, C410.2, C411.2, D401.2 (A2), D402.2 (A2), D405.1 (K), E101.3, E201.3, J3.2 (Ext), PS1.7 (COM), R302.2, R404.2, R406.2, RV101.2, RV101.3, RV201.2, RV201.3, U4.4 (GND), U4.9 (EP), U5.4 (GND), U5.9 (EP)

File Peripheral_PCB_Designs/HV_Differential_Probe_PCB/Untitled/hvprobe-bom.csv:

Qty,References,Value,Footprint,Part / spec,DNP
1,J1,HV_IN_P,TestPoint:TestPoint_THTPad_D4.0mm_Drill2.0mm,,
2,R101 R201,330,Resistor_SMD:R_2512_6332Metric,1 W thick film 2512,
20,R102 R103 R104 R105 R106 R107 R108 R109 R110 R111 R202 R203 R204 R205 R206 R207 R208 R209 R210 R211,10M,Resistor_SMD:R_2512_6332Metric,Vishay CRHV2512AF10M0FKE5,
20,C101 C102 C103 C104 C105 C106 C107 C108 C109 C110 C201 C202 C203 C204 C205 C206 C207 C208 C209 C210,22pF 2kV,Capacitor_SMD:C_1206_3216Metric,KEMET C1206C220JGGACTU,
2,R112 R212,97.6k 0.1%,Resistor_SMD:R_0805_2012Metric,0.1 % 25 ppm thin film,
2,RV101 RV201,5k,Potentiometer_THT:Potentiometer_Bourns_3296W_Vertical,Bourns 3296W-1-502LF,
2,C111 C211,2.2nF C0G 1%,Capacitor_SMD:C_1206_3216Metric,C0G 1 % 50 V 1206,
2,C112 C212,SOT 0-150pF,Capacitor_SMD:C_0805_2012Metric,,DNP
2,C113 C213,5-30pF,Capacitor_SMD:C_Trimmer_Murata_TZB4-A,Murata TZB4Z300AB10R00,
2,E101 E201,90V GDT,hvprobe:GDT_Bourns_2051,Bourns 2051-09-SM-RPLF,
2,R113 R213,100,Resistor_SMD:R_0603_1608Metric,,
2,D101 D201,BAV199,Package_TO_SOT_SMD:SOT-23,Nexperia BAV199,
3,U1 U2 U3,THS4631D,Package_SO:SOIC-8_3.9x4.9mm_P1.27mm,TI THS4631DR,
6,C114 C115 C214 C215 C301 C302,100nF,Capacitor_SMD:C_0603_1608Metric,,
1,J2,HV_IN_N,TestPoint:TestPoint_THTPad_D4.0mm_Drill2.0mm,,
1,R301,1.00k 0.1%,Resistor_SMD:R_0805_2012Metric,0.1 % 10 ppm thin film; match all four,
3,R302 R303 R304,1.00k 0.1%,Resistor_SMD:R_0805_2012Metric,,
1,R305,1M,Resistor_SMD:R_0603_1608Metric,,
1,RV301,10k,Potentiometer_THT:Potentiometer_Bourns_3296W_Vertical,Bourns 3296W-1-103LF,
1,R306,49.9,Resistor_SMD:R_0603_1608Metric,,
1,J3,OUT,hvprobe:Coax_Solder_Pads,,
2,D401 D402,SMAJ15CA,Diode_SMD:D_SMA,,
1,J4,BATT 4.5-9V,Connector_JST:JST_PH_B2B-PH-K_1x02_P2.00mm_Vertical,,
1,J5,USB-C 5V,Connector_USB:USB_C_Receptacle_GCT_USB4125-xx-x_6P_TopMnt_Horizontal,,
2,R401 R402,5.1k,Resistor_SMD:R_0603_1608Metric,,
2,D403 D404,B5819W,Diode_SMD:D_SOD-123,,
1,SW1,POWER,Button_Switch_SMD:SW_SPDT_PCM12,,
5,C401 C404 C405 C408 C411,10uF 25V,Capacitor_SMD:C_1206_3216Metric,,
1,PS1,TMR 3-0523,hvprobe:Traco_TMR3_SIP8,Traco TMR 3-0523,
2,C402 C403,1uF 25V,Capacitor_SMD:C_0805_2012Metric,,
2,FB401 FB402,600R@100MHz,Inductor_SMD:L_0805_2012Metric,,
1,U4,TPS7A4901DGNR,Package_SO:MSOP-8-1EP_3x3mm_P0.65mm_EP1.68x1.88mm,TI TPS7A4901DGNR,
2,R403 R405,90.9k,Resistor_SMD:R_0603_1608Metric,,
2,R404 R406,10k,Resistor_SMD:R_0603_1608Metric,,
4,C406 C407 C409 C410,10nF,Capacitor_SMD:C_0603_1608Metric,,
1,U5,TPS7A3001DGNR,Package_SO:MSOP-8-1EP_3x3mm_P0.65mm_EP1.68x1.88mm,TI TPS7A3001DGNR,
1,R407,4.7k,Resistor_SMD:R_0603_1608Metric,,
1,D405,GRN,LED_SMD:LED_0805_2012Metric,,

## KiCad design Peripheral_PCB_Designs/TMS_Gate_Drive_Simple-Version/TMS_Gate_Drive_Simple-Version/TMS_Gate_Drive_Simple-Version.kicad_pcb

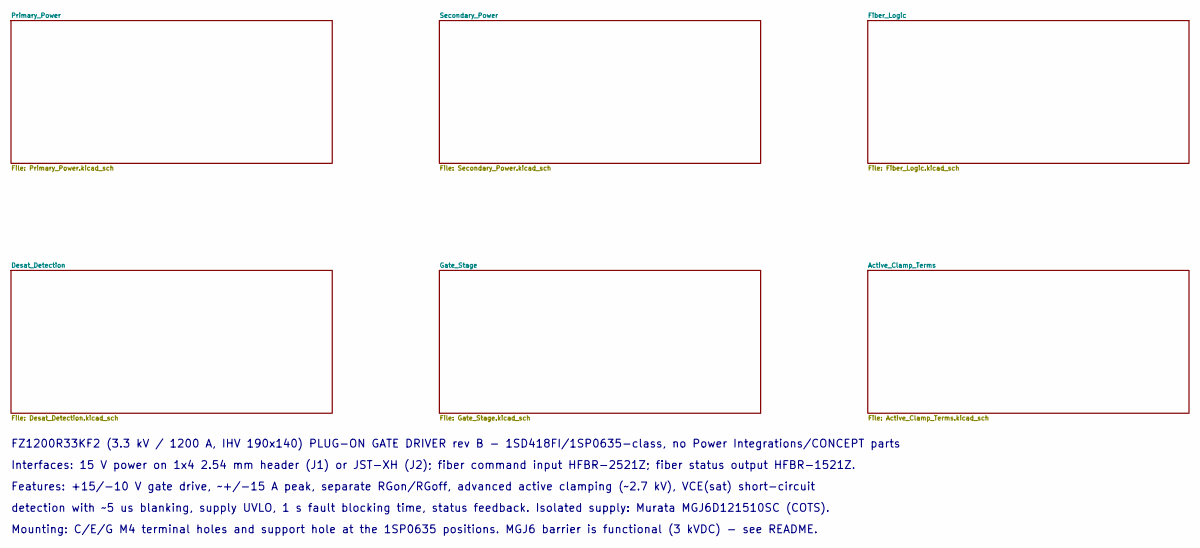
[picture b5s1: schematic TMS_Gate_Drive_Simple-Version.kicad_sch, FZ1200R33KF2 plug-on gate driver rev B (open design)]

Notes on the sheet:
FZ1200R33KF2 (3.3 kV / 1200 A, IHV 190x140) PLUG-ON GATE DRIVER rev B - 1SD418FI/1SP0635-class, no Power Integrations/CONCEPT parts
Mounting: C/E/G M4 terminal holes and support hole at the 1SP0635 positions. MGJ6 barrier is functional (3 kVDC) - see README.
Features: +15/-10 V gate drive, ~+/-15 A peak, separate RGon/RGoff, advanced active clamping (~2.7 kV), VCE(sat) short-circuit
Interfaces: 15 V power on 1x4 2.54 mm header (J1) or JST-XH (J2); fiber command input HFBR-2521Z; fiber status output HFBR-1521Z.
detection with ~5 us blanking, supply UVLO, 1 s fault blocking time, status feedback. Isolated supply: Murata MGJ6D121510SC (COTS).
